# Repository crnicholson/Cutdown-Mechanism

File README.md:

# Cutdown Mechanism
This cutdown mechanism is for a [high-altitude glider, named StratoSoar](https://github.com/crnicholson/StratoSoar-MK2). It is for releasing the glider from the high-altitude balloon payload, so it can fly down to the ground.

## Components
The cutdown mechanism consists of a few basic components, all easy to get and cheap.

- The PCB (more on this later).
- A SG90 standard blue servo.
- Arduino Nano.
- BME280 breakout board.
- A variety of headers.
- 9V battery clip.
- 9V battery.
- SPDT breadboard switches.
- One 10 K resistors.
- One standard 6 mm button. 

## Tools

## PCB

## 3D Printing

## Assembly 

## Usage

## Funding 
SratoSoar currently has very limited funding to complete this project. We would love any outside support we could get to elevate (no pun intended) this project to the next level. Reach out to me if you have interest at:

- [newbsballoons@gmail.com](mailto:newbsballoons@gmail.com)  (organization email, recommended).
- [charlienicholsonr@gmail.com](mailto:charlienicholsonr@gmail.com)  (personal email).

## Still Have Questions?
Do you have any questions? Are the docs incomplete and you want to ask anything? Do you just want to say hi?

Reach out to me at [charlienicholsonr@gmail.com](mailto:charlienicholsonr@gmail.com).

## License
Both the software and documentation are under the [GNU GPL v3 license](https://choosealicense.com/licenses/gpl-3.0/). The hardware and the 3D files are under the [CERN Open Hardware Licence Version 2 - Strongly Reciprocal](https://choosealicense.com/licenses/cern-ohl-s-2.0/). The media will be licensed under the [CC BY 4.0 DEED](https://creativecommons.org/licenses/by/4.0/).

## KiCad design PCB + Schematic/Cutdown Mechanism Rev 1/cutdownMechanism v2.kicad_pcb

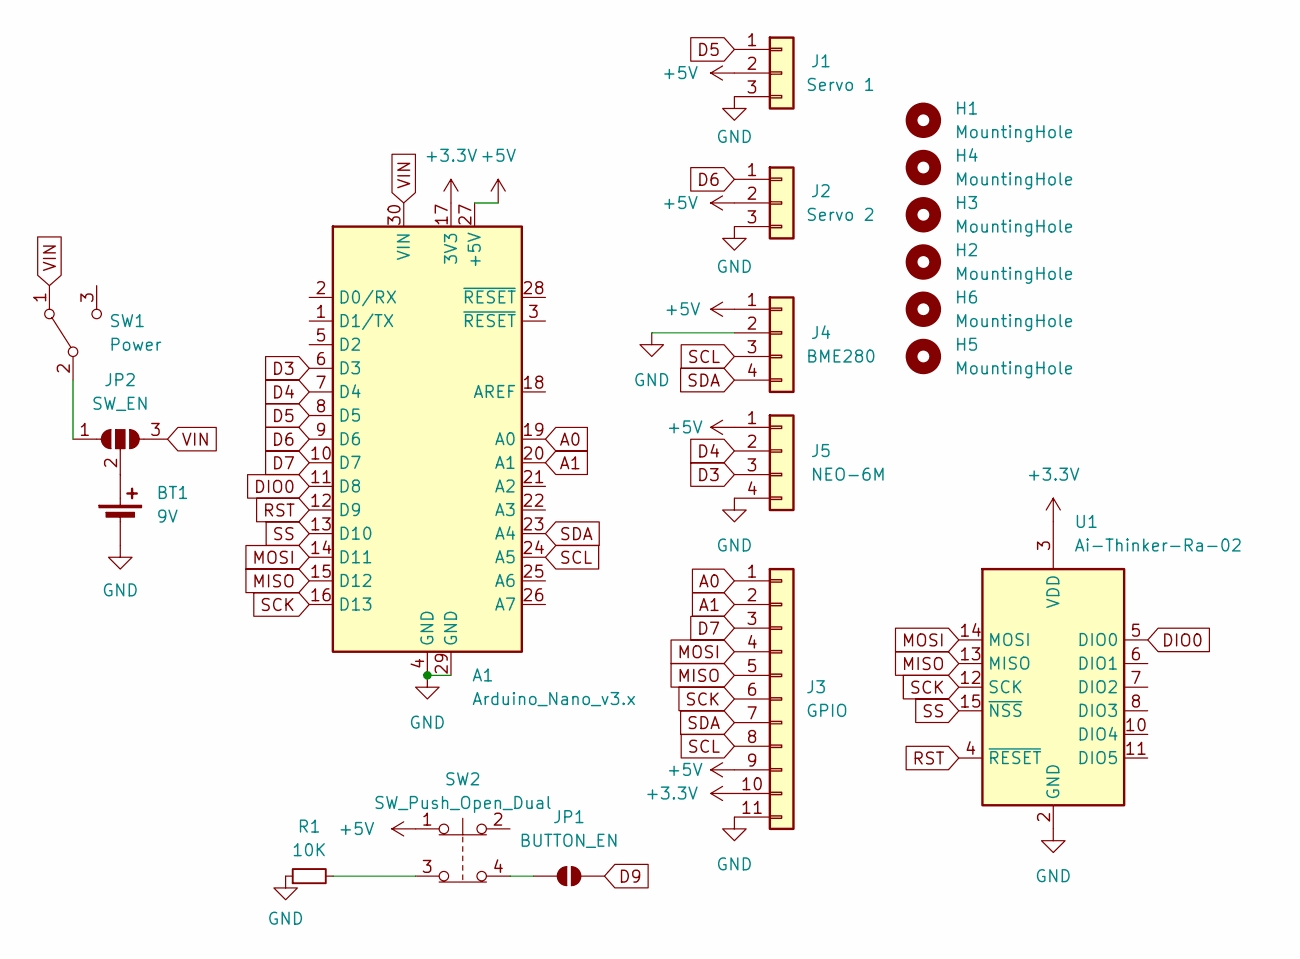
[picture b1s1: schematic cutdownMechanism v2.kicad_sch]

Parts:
A1: Arduino_Nano_v3.x; Arduino_Nano
BT1: 9V; PinHeader_1x02_P2.54mm_Vertical
H1, H2, H3, H4, H5, H6: MountingHole; MountingHole_2.2mm_M2
J1: Servo 1; PinHeader_1x03_P2.54mm_Vertical
J2: Servo 2; PinHeader_1x03_P2.54mm_Vertical
J3: GPIO; PinHeader_1x11_P2.54mm_Vertical
J4: BME280; PinHeader_1x04_P2.54mm_Vertical
J5: NEO-6M; PinHeader_1x04_P2.54mm_Vertical
JP1: BUTTON_EN; SolderJumper-2_P1.3mm_Open_RoundedPad1.0x1.5mm
JP2: SW_EN; SolderJumper-3_P1.3mm_Open_RoundedPad1.0x1.5mm_NumberLabels
R1: 10K; R_Axial_DIN0207_L6.3mm_D2.5mm_P10.16mm_Horizontal
SW1: Power; SW_SPDT
SW2: SW_Push_Open_Dual; SW_PUSH_6mm
U1: Ai-Thinker-Ra-02; LoRa module

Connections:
+3.3V: A1.17 (3V3), J3.10, U1.3 (VDD)
+5V: A1.27 (+5V), J1.2, J2.2, J3.9, J4.1, J5.1, SW2.1
A0: A1.19 (A0), J3.1
A1: A1.20 (A1), J3.2
D3: A1.6 (D3), J5.3
D4: A1.7 (D4), J5.2
D5: A1.8 (D5), J1.1
D6: A1.9 (D6), J2.1
D7: A1.10 (D7), J3.3
D9: JP1.2 (B)
DIO0: A1.11 (D8), U1.5 (DIO0)
GND: A1.4 (GND), A1.29 (GND), BT1.2 (-), J1.3, J2.3, J3.11, J4.2, J5.4, R1.1, U1.1 (GND), U1.2 (GND), U1.9 (GND), U1.16 (GND)
MISO: A1.15 (D12), J3.5, U1.13 (MISO)
MOSI: A1.14 (D11), J3.4, U1.14 (MOSI)
unnamed: BT1.1 (+), JP2.2 (C)
unnamed: JP1.1 (A), SW2.4
unnamed: JP2.1 (A), SW1.2 (B)
unnamed: R1.2, SW2.3
RST: A1.12 (D9), U1.4 (~RESET)
SCK: A1.16 (D13), J3.6, U1.12 (SCK)
SCL: A1.24 (A5), J3.8, J4.3
SDA: A1.23 (A4), J3.7, J4.4
SS: A1.13 (D10), U1.15 (~NSS)
VIN: A1.30 (VIN), JP2.3 (B), SW1.1 (A)

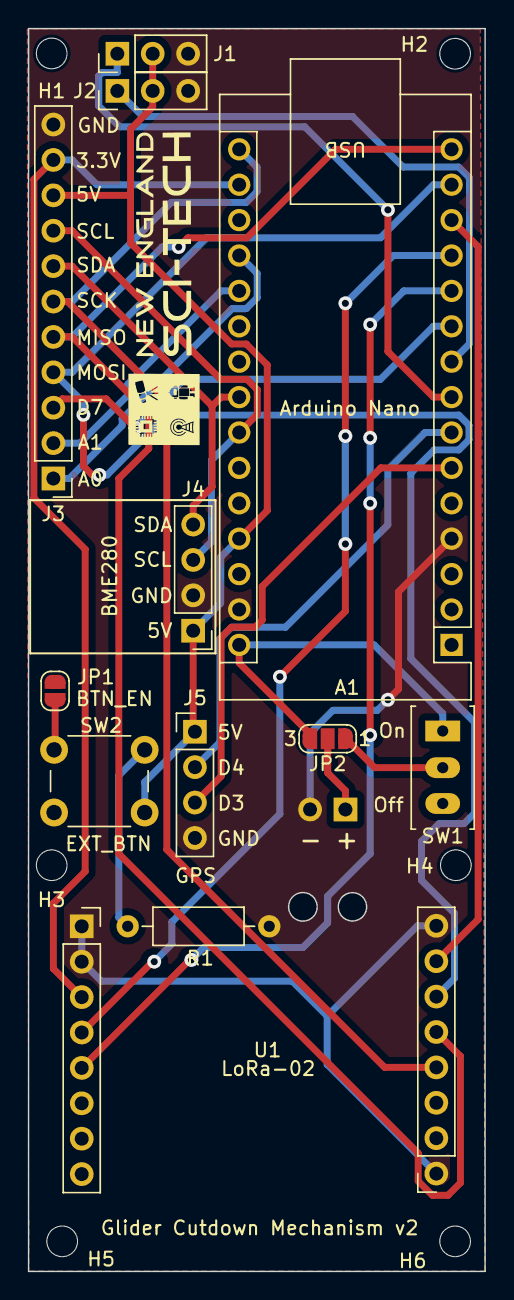
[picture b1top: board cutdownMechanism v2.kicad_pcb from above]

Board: 2 copper layers, 32.8 x 89.2 mm, 19 parts (1 on the bottom side), 23 nets.

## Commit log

2024-03-02 Create
2024-03-02 Create LICENSE
2024-03-02 Add PCB files
2024-03-02 Rename cutdownMechanism.kicad_pcb to PCB + Schematic/cutdownMechanism.kicad_pcb
2024-03-02 Rename cutdownMechanism.kicad_pro to PCB + Schematic/cutdownMechanism.kicad_pro
2024-03-02 Rename cutdownMechanism.kicad_sch to PCB + Schematic/cutdownMechanism.kicad_sch
2024-03-02 Rename cutdownMechanism.kicad_pro to cutdownMechanism.kicad_pro
2024-03-02 Create licenses
2024-04-16 Update PCB anf gitignore
2024-05-06 Update GPS and PCB
2024-05-21 Fixed some bugs
2024-05-24 Minor updates
